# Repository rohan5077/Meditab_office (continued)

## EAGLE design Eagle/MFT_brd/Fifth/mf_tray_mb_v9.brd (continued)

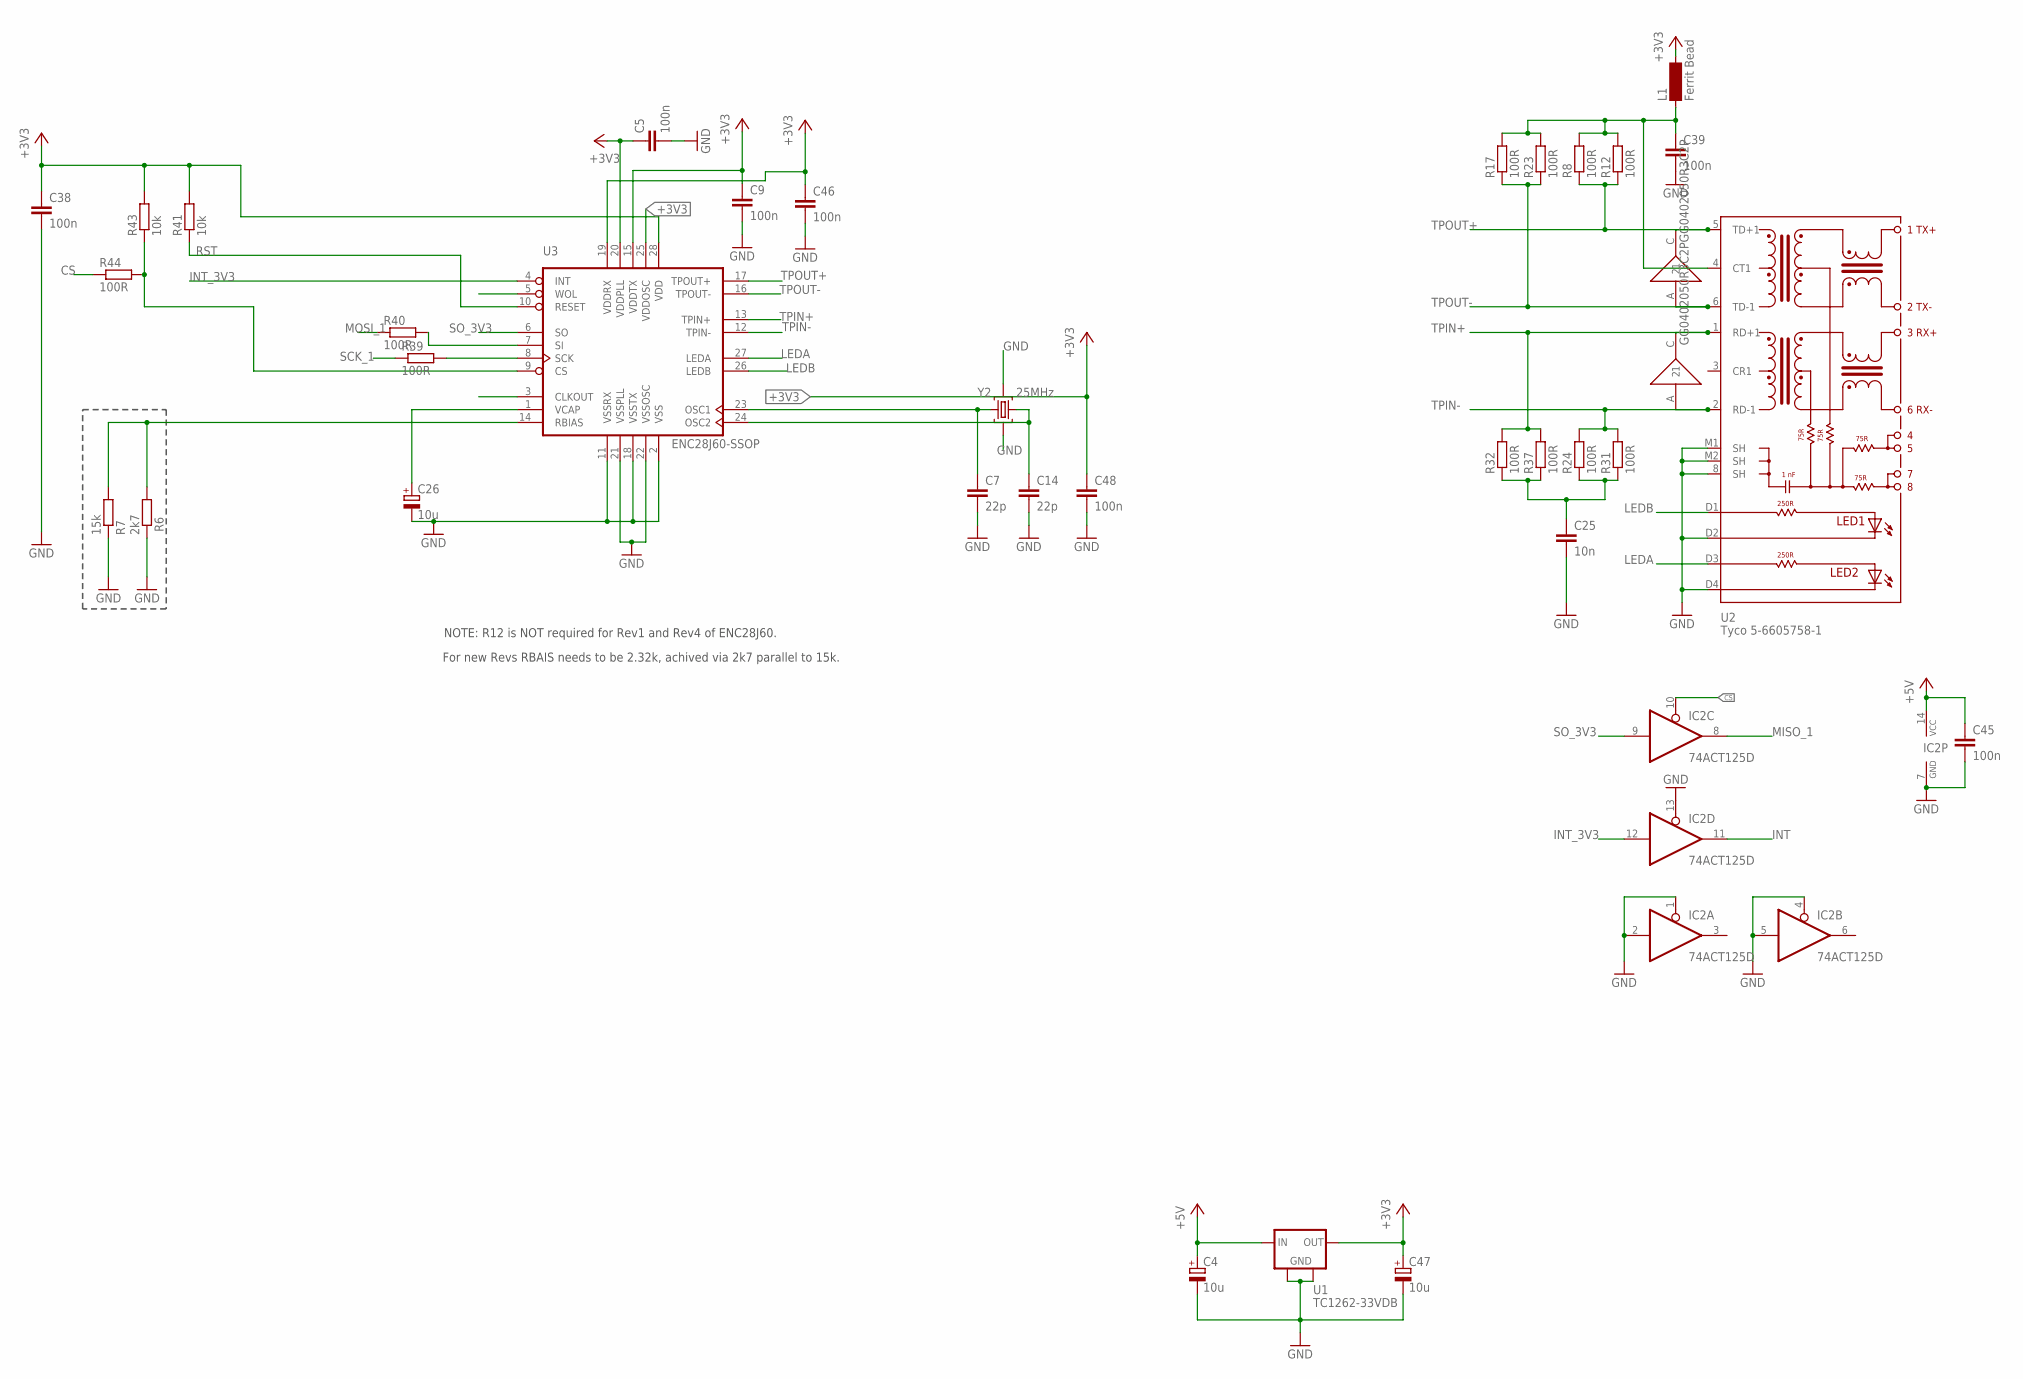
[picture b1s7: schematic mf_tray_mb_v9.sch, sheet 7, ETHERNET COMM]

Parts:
C4, C26, C47: 10u; 153CLV-0605
C5, C9, C38, C39, C45, C46, C48: 100n; C0603
C7, C14: 22p; C0603
C25: 10n; C0603
IC2: 74ACT125D; SO14
L1: Ferrit Bead; SM-1206
R6: 2k7; R0603
R7: 15k; R0603
R8, R12, R17, R23, R24, R31, R32, R37, R39, R40, R44: 100R; R0603
R41, R43: 10k; R0603
U1: TC1262-33VDB; SOT223
U2: Tyco 5-6605758-1; 5-6605758-1
U3: ENC28J60-SSOP; SSOP28
U$6, U$7: GG0402050R3C2P; 0402
Y2: 25MHz; CRYSTAL-3.2-2.5

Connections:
+3V3: C5.1, C9.1, C38.1, C46.1, C47.+, C48.1, L1.2, R41.2, R43.2, U1.3 (OUT), U3.15 (VDDTX), U3.19 (VDDRX), U3.20 (VDDPLL), U3.25 (VDDOSC), U3.28 (VDD); also elsewhere on the board
+5V: C4.+, C45.1, IC2.14 (VCC), U1.1 (IN); also elsewhere on the board
CS: IC2.10 (OE), R44.2; also elsewhere on the board
GND: C4.-, C5.2, C7.2, C9.2, C14.2, C25.2, C26.-, C38.2, C39.2, C45.2, C46.2, C47.-, C48.2, IC2.1 (OE), IC2.2 (I), IC2.4 (OE), IC2.5 (I), IC2.7 (GND), IC2.13 (OE), R6.2, R7.2, U1.2 (GND), U1.4 (GND), U2.8 (SH), U2.D2, U2.D4, U2.M1 (SH), U2.M2 (SH), U3.2 (VSS), U3.11 (VSSRX), U3.18 (VSSTX), U3.21 (VSSPLL), U3.22 (VSSOSC), Y2.2 (GND), Y2.4 (GND); also elsewhere on the board
INT: IC2.11 (O); also elsewhere on the board
INT_3V3: IC2.12 (I), U3.4 (INT)
LEDA: U2.D3, U3.27 (LEDA)
LEDB: U2.D1, U3.26 (LEDB)
MISO_1: IC2.8 (O); also elsewhere on the board
MOSI_1: R40.2; also elsewhere on the board
unnamed: R6.1, R7.1, U3.14 (RBIAS)
unnamed: C7.1, U3.23 (OSC1), Y2.3 (C2)
unnamed: C25.1, R24.1, R31.1, R32.1, R37.1
unnamed: C39.1, L1.1, R8.2, R12.2, R17.2, R23.2, U2.4 (CT1)
unnamed: C14.1, U3.24 (OSC2), Y2.1 (C1)
unnamed: R43.1, R44.1, U3.9 (CS)
unnamed: R40.1, U3.7 (SI)
unnamed: R39.1, U3.8 (SCK)
unnamed: C26.+, U3.1 (VCAP)
RST: R41.1, U3.10 (RESET)
SCK_1: R39.2; also elsewhere on the board
SO_3V3: IC2.9 (I), U3.6 (SO)
TPIN+: R32.2, R37.2, U2.1 (RD+1), U3.13 (TPIN+), U$7.C (2)
TPIN-: R24.2, R31.2, U2.2 (RD-1), U3.12 (TPIN-), U$7.A (1)
TPOUT+: R8.1, R12.1, U2.5 (TD+1), U3.17 (TPOUT+), U$6.C (2)
TPOUT-: R17.1, R23.1, U2.6 (TD-1), U3.16 (TPOUT-), U$6.A (1)

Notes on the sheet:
NOTE: R12 is NOT required for Rev1 and Rev4 of ENC28J60.
For new Revs RBAIS needs to be 2.32k, achived via 2k7 parallel to 15k.

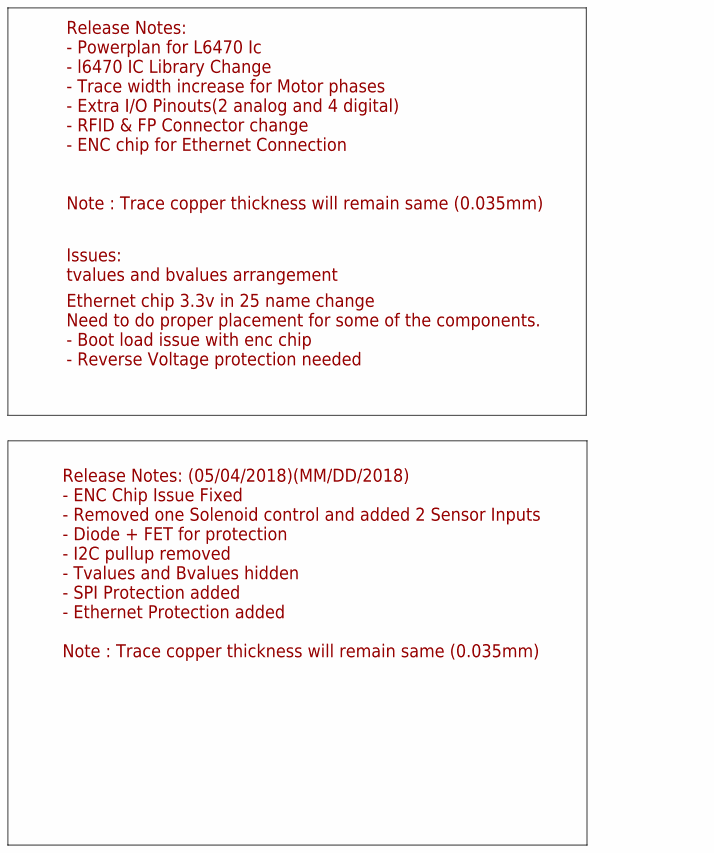
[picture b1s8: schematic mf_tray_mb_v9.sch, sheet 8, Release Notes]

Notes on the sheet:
Release Notes: - Powerplan for L6470 Ic - l6470 IC Library Change - Trace width increase for Motor phases - Extra I/O Pinouts(2 analog and 4 digital) - RFID & FP Connector change - ENC chip for Ethernet Connection Note : Trace copper thickness will remain same (0.035mm)
Issues:
tvalues and bvalues arrangement
Ethernet chip 3.3v in 25 name change
Need to do proper placement for some of the components.
- Boot load issue with enc chip
- Reverse Voltage protection needed
Release Notes: (05/04/2018)(MM/DD/2018) - ENC Chip Issue Fixed - Removed one Solenoid control and added 2 Sensor Inputs - Diode + FET for protection - I2C pullup removed - Tvalues and Bvalues hidden - SPI Protection added - Ethernet Protection added Note : Trace copper thickness will remain same (0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

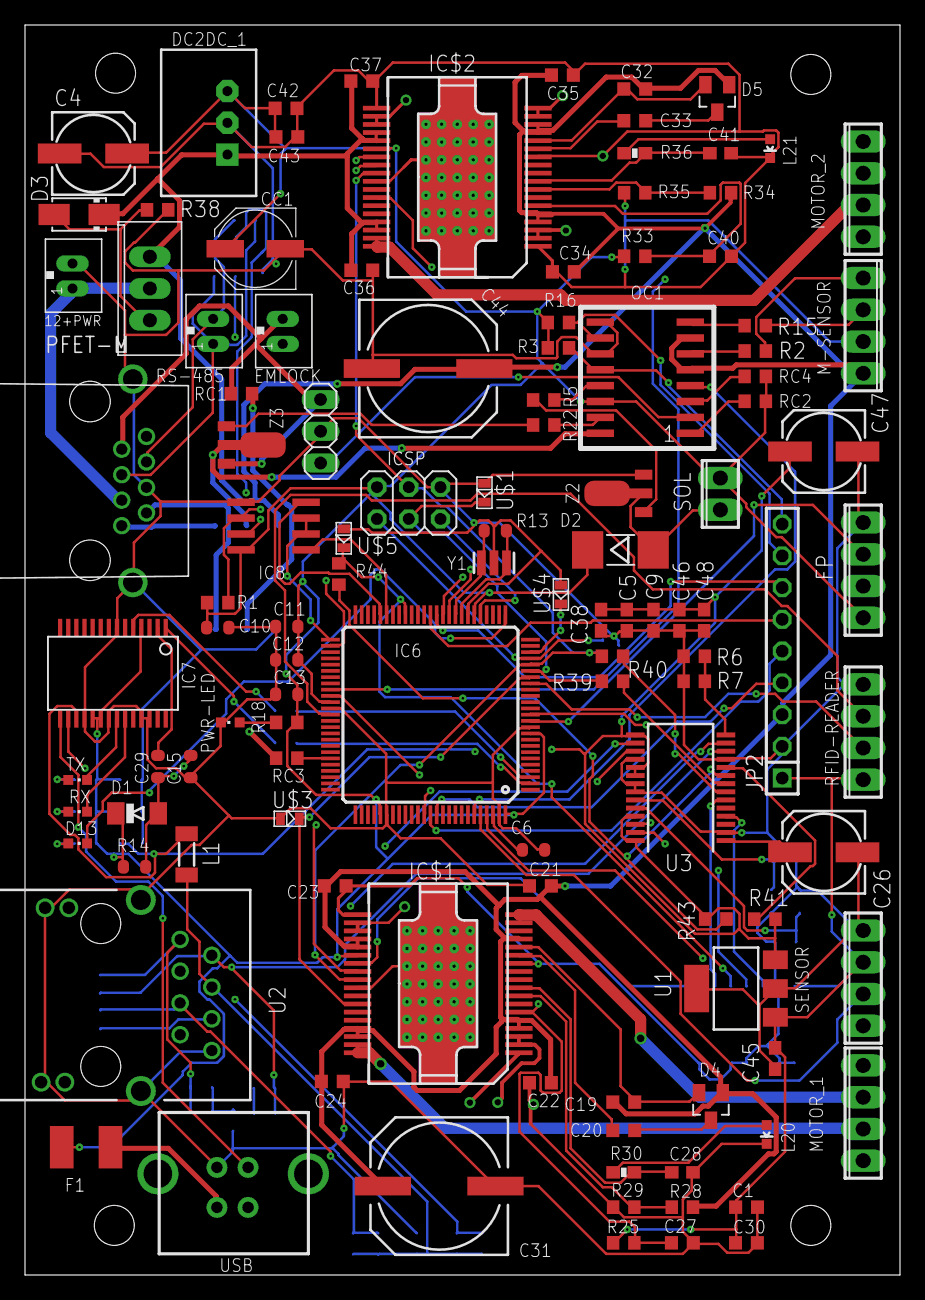
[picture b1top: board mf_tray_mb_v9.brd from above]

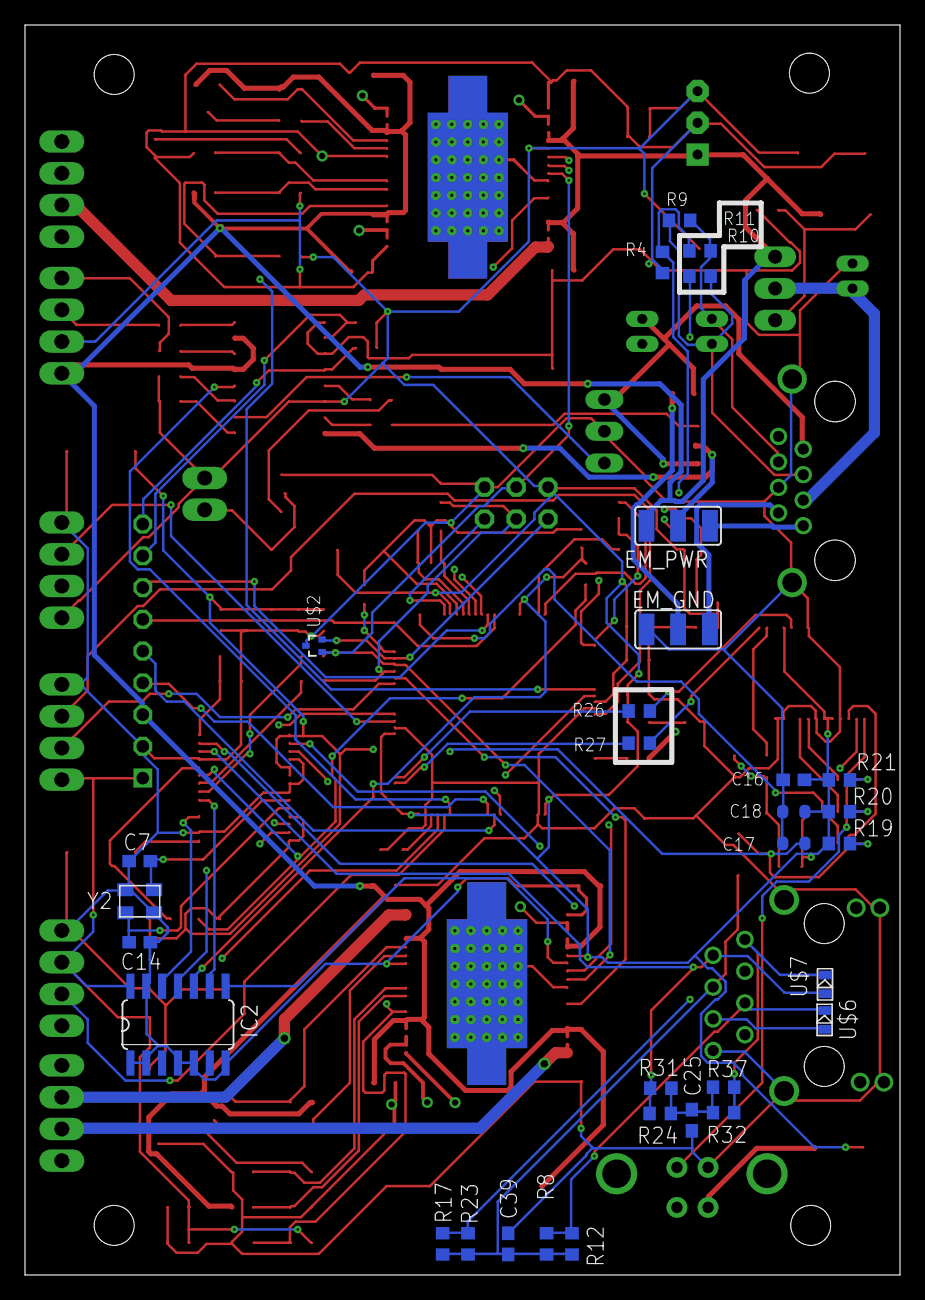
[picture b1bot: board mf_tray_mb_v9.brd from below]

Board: 4 copper layers, 70.0 x 100.0 mm, 146 parts (31 on the bottom side), 111 nets.

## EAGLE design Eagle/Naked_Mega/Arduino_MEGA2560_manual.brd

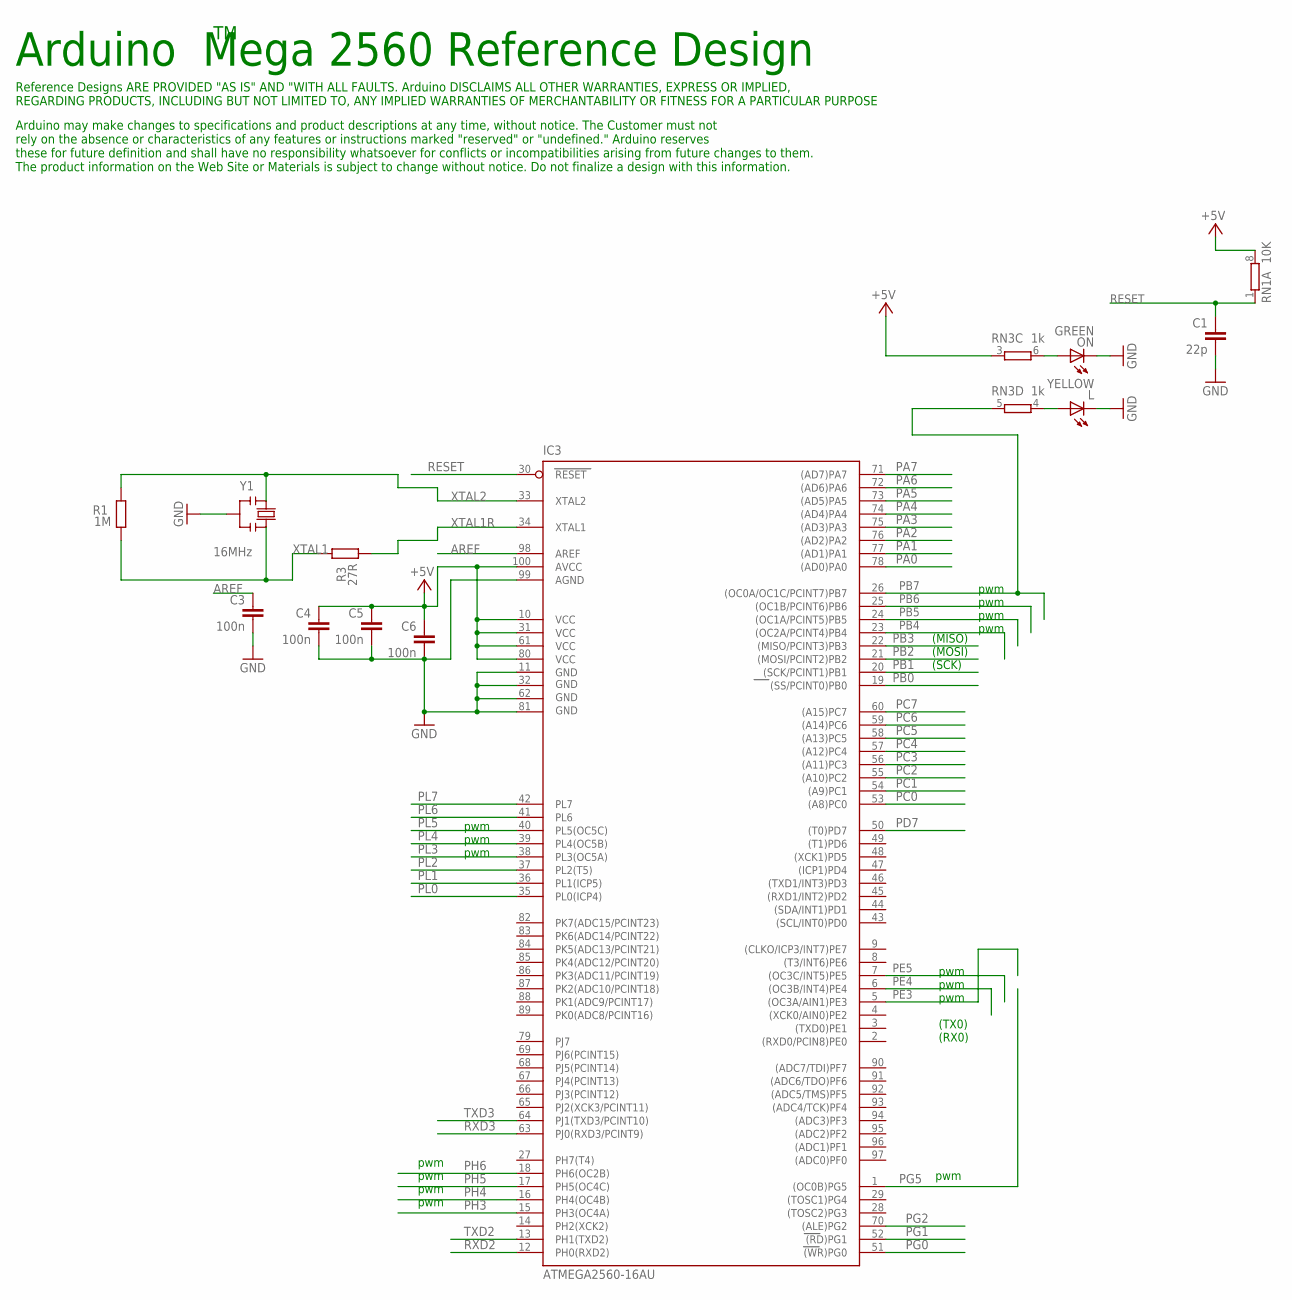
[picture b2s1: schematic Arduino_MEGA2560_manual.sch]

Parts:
C1: 22p; C0603-ROUND
C3, C4, C5, C6: 100n; C0603-ROUND
IC3: ATMEGA2560-16AU; TQFP100
L: YELLOW; CHIP-LED0805
ON: GREEN; CHIP-LED0805
R1: 1M; R0603-ROUND
R3: 27R; R0603-ROUND
RN1: 10K; CAT16
RN3: 1k; CAY16
Y1: 16MHz; RESONATOR

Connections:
+5V: C4.1, C5.1, C6.1, IC3.10 (VCC), IC3.31 (VCC1), IC3.61 (VCC2), IC3.80 (VCC3), IC3.100 (AVCC), RN1.8 (2), RN3.3 (1)
AREF: C3.1, IC3.98 (AREF)
GND: C1.2, C3.2, C4.2, C5.2, C6.2, IC3.11 (GND), IC3.32 (GND1), IC3.62 (GND2), IC3.81 (GND3), IC3.99 (AGND), L.C, ON.C, Y1.2
unnamed: L.A, RN3.4 (1)
unnamed: ON.A, RN3.6 (2)
PA0: IC3.78 ((AD0)PA0)
PA1: IC3.77 ((AD1)PA1)
PA2: IC3.76 ((AD2)PA2)
PA3: IC3.75 ((AD3)PA3)
PA4: IC3.74 ((AD4)PA4)
PA5: IC3.73 ((AD5)PA5)
PA6: IC3.72 ((AD6)PA6)
PA7: IC3.71 ((AD7)PA7)
PB0: IC3.19 ((SS/PCINT0)PB0)
PB1: IC3.20 ((SCK/PCINT1)PB1)
PB2: IC3.21 ((MOSI/PCINT2)PB2)
PB3: IC3.22 ((MISO/PCINT3)PB3)
PB4: IC3.23 ((OC2A/PCINT4)PB4)
PB5: IC3.24 ((OC1A/PCINT5)PB5)
PB6: IC3.25 ((OC1B/PCINT6)PB6)
PB7: IC3.26 ((OC0A/OC1C/PCINT7)PB7), RN3.5 (2)
PC0: IC3.53 ((A8)PC0)
PC1: IC3.54 ((A9)PC1)
PC2: IC3.55 ((A10)PC2)
PC3: IC3.56 ((A11)PC3)
PC4: IC3.57 ((A12)PC4)
PC5: IC3.58 ((A13)PC5)
PC6: IC3.59 ((A14)PC6)
PC7: IC3.60 ((A15)PC7)
PD7: IC3.50 ((T0)PD7)
PE3: IC3.5 ((OC3A/AIN1)PE3)
PE4: IC3.6 ((OC3B/INT4)PE4)
PE5: IC3.7 ((OC3C/INT5)PE5)
PG0: IC3.51 ((WR)PG0)
PG1: IC3.52 ((RD)PG1)
PG2: IC3.70 ((ALE)PG2)
PG5: IC3.1 ((OC0B)PG5)
PH3: IC3.15 (PH3(OC4A))
PH4: IC3.16 (PH4(OC4B))
PH5: IC3.17 (PH5(OC4C))
PH6: IC3.18 (PH6(OC2B))
PL0: IC3.35 (PL0(ICP4))
PL1: IC3.36 (PL1(ICP5))
PL2: IC3.37 (PL2(T5))
PL3: IC3.38 (PL3(OC5A))
PL4: IC3.39 (PL4(OC5B))
PL5: IC3.40 (PL5(OC5C))
PL6: IC3.41 (PL6)
PL7: IC3.42 (PL7)
RESET: C1.1, IC3.30 (RESET), RN1.1
RXD2: IC3.12 (PH0(RXD2))
RXD3: IC3.63 (PJ0(RXD3/PCINT9))
TXD2: IC3.13 (PH1(TXD2))
TXD3: IC3.64 (PJ1(TXD3/PCINT10))
XTAL1: R1.1, R3.2, Y1.3
XTAL1R: IC3.34 (XTAL1), R3.1
XTAL2: IC3.33 (XTAL2), R1.2, Y1.1

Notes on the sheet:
pwm
(TX0)
(RX0)
(MISO)
(SCK)
(MOSI)
Arduino Mega 2560 Reference Design
Arduino may make changes to specifications and product descriptions at any time, without notice. The Customer must not rely on the absence or characteristics of any features or instructions marked "reserved" or "undefined." Arduino reserves these for future definition and shall have no responsibili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
Reference Designs ARE PROVIDED "AS IS" AND "WITH ALL FAULTS. Arduino DISCLAIMS ALL OTHER WARRANTIES, EXPRESS OR IMPLIED, REGARDING PRODUCTS, INCLUDING BUT NOT LIMITED TO, ANY IMPLIED WARRANTIES OF MERCHANTABILITY OR FITNESS FOR A PARTICULAR PURPOSE

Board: 2 copper layers, 13 parts (0 on the bottom side), 10 nets, no tracks yet.

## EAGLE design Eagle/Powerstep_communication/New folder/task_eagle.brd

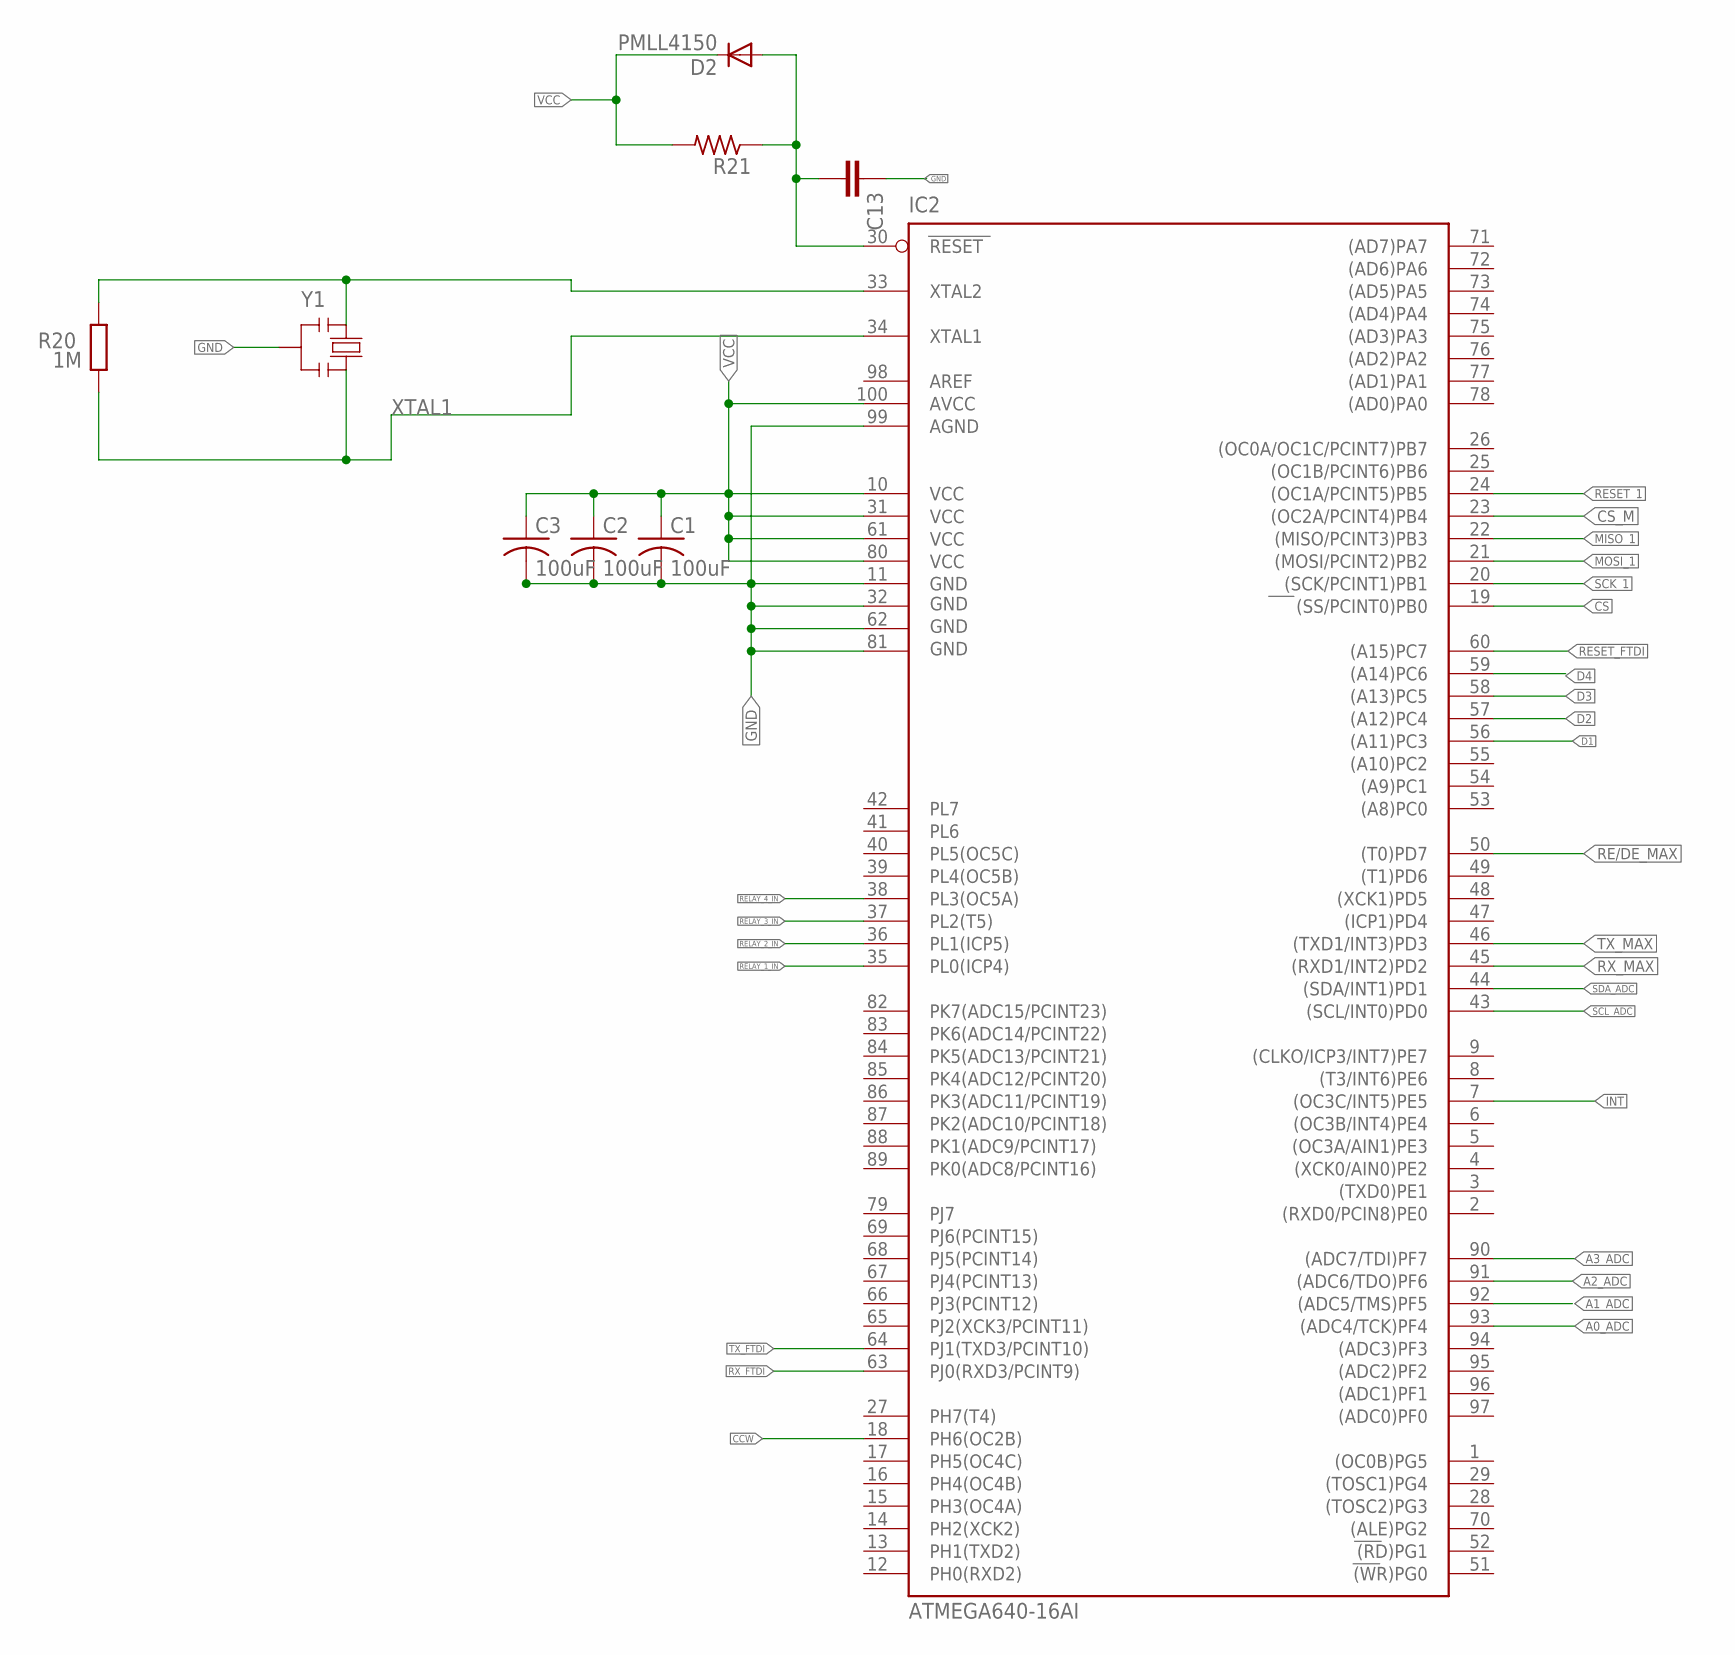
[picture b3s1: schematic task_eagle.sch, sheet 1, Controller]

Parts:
C1, C2, C3: 100uF; C0603
C13: CC0603; C0603
D2: PMLL4150; SOD80C
IC2: ATMEGA640-16AI; TQFP100
R20: 1M; R0603-ROUND
R21: R-US_R0603; R0603
Y1: RESONATORMU; RESONATOR

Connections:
CCW: IC2.18 (PH6(OC2B)); also elsewhere on the board
CS: IC2.19 ((SS/PCINT0)PB0); also elsewhere on the board
CS_M: IC2.23 ((OC2A/PCINT4)PB4); also elsewhere on the board
D1: IC2.56 ((A11)PC3); also elsewhere on the board
D2: IC2.57 ((A12)PC4); also elsewhere on the board
D3: IC2.58 ((A13)PC5); also elsewhere on the board
D4: IC2.59 ((A14)PC6); also elsewhere on the board
GND: C1.2, C2.2, C3.2, C13.1, IC2.11 (GND), IC2.32 (GND1), IC2.62 (GND2), IC2.81 (GND3), IC2.99 (AGND), Y1.2; also elsewhere on the board
INT: IC2.7 ((OC3C/INT5)PE5); also elsewhere on the board
MISO_1: IC2.22 ((MISO/PCINT3)PB3); also elsewhere on the board
MOSI_1: IC2.21 ((MOSI/PCINT2)PB2); also elsewhere on the board
unnamed: C13.2, D2.A, IC2.30 (RESET), R21.1
RE/DE_MAX: IC2.50 ((T0)PD7); also elsewhere on the board
RELAY_1_IN: IC2.35 (PL0(ICP4)); also elsewhere on the board
RELAY_2_IN: IC2.36 (PL1(ICP5)); also elsewhere on the board
RELAY_3_IN: IC2.37 (PL2(T5)); also elsewhere on the board
RELAY_4_IN: IC2.38 (PL3(OC5A)); also elsewhere on the board
RESET_1: IC2.24 ((OC1A/PCINT5)PB5); also elsewhere on the board
RESET_FTDI: IC2.60 ((A15)PC7); also elsewhere on the board
RX_FTDI: IC2.63 (PJ0(RXD3/PCINT9)); also elsewhere on the board
RX_MAX: IC2.45 ((RXD1/INT2)PD2); also elsewhere on the board
SCK_1: IC2.20 ((SCK/PCINT1)PB1); also elsewhere on the board
SCL_ADC: IC2.43 ((SCL/INT0)PD0); also elsewhere on the board
SDA_ADC: IC2.44 ((SDA/INT1)PD1); also elsewhere on the board
TX_FTDI: IC2.64 (PJ1(TXD3/PCINT10)); also elsewhere on the board
TX_MAX: IC2.46 ((TXD1/INT3)PD3); also elsewhere on the board
XTAL1: IC2.34 (XTAL1), R20.1, Y1.3
XTAL2: IC2.33 (XTAL2), R20.2, Y1.1

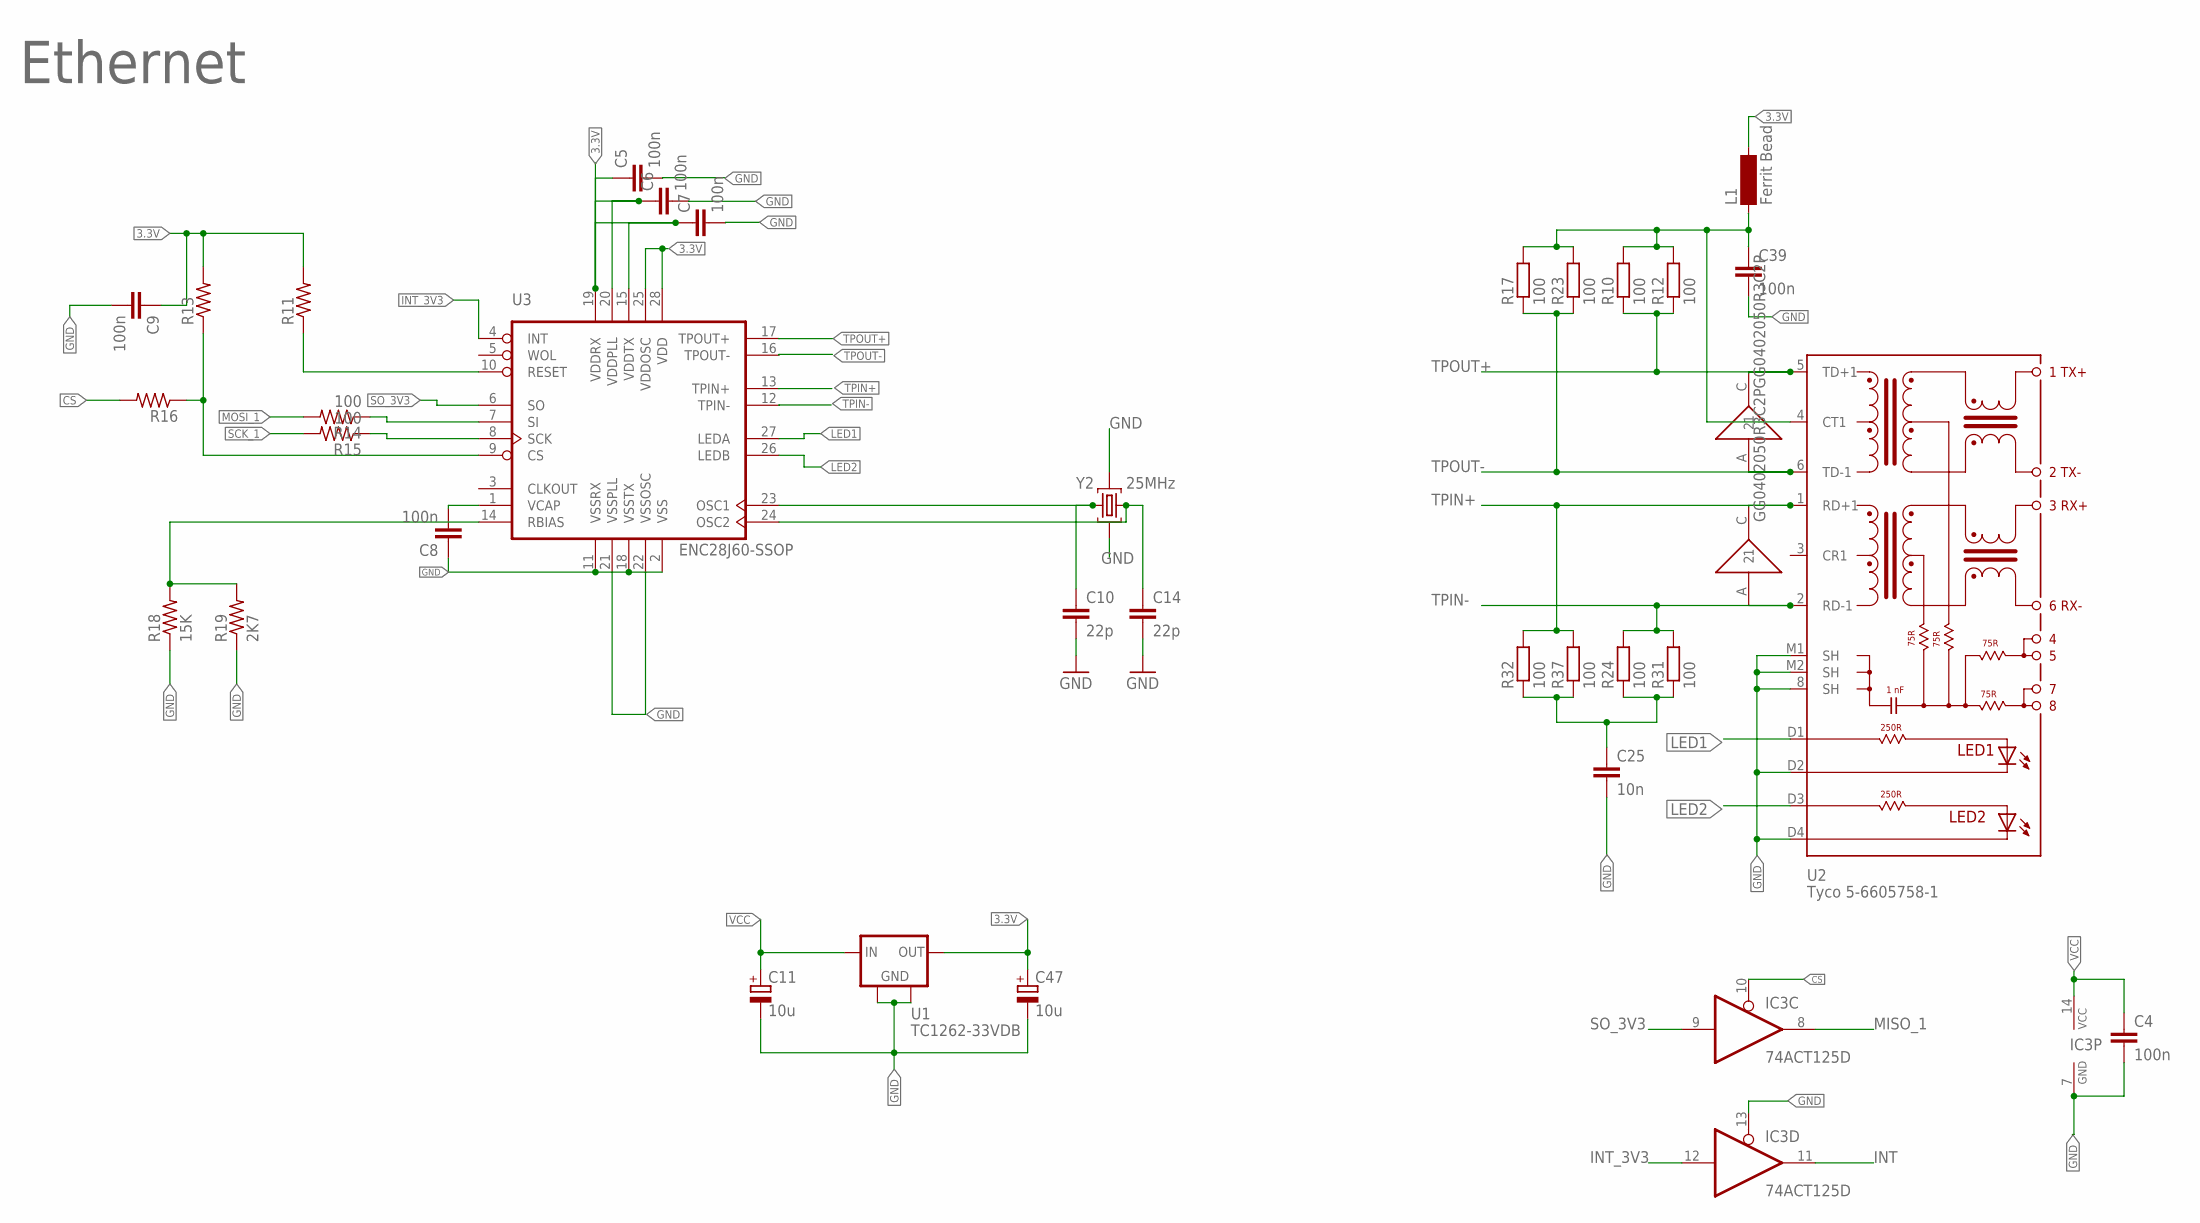
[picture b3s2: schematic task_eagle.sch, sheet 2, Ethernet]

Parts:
C4, C5, C6, C7, C8, C9, C39: 100n; C0603
C10, C14: 22p; C0603
C11, C47: 10u; 153CLV-0605
C25: 10n; C0603
IC3: 74ACT125D; SO14
L1: Ferrit Bead; SM-1206
R10, R12, R14, R15, R17, R23, R24, R31, R32, R37: 100; R0603
R11, R13, R16: R-US_R0603; R0603
R18: 15K; R0603
R19: 2K7; R0603
U1: TC1262-33VDB; SOT223
U2: Tyco 5-6605758-1; 5-6605758-1
U3: ENC28J60-SSOP; SSOP28
U$6, U$7: GG0402050R3C2P; 0402
Y2: 25MHz; CRYSTAL-3.2-2.5

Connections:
3.3V: C5.1, C6.1, C7.1, C9.1, C47.+, L1.2, R11.2, R13.2, U1.3 (OUT), U3.15 (VDDTX), U3.19 (VDDRX), U3.20 (VDDPLL), U3.25 (VDDOSC), U3.28 (VDD); also elsewhere on the board
CS: IC3.10 (OE), R16.2; also elsewhere on the board
GND: C4.2, C5.2, C6.2, C7.2, C8.1, C9.2, C10.2, C11.-, C14.2, C25.2, C39.2, C47.-, IC3.7 (GND), IC3.13 (OE), R18.1, R19.1, U1.2 (GND), U1.4 (GND), U2.8 (SH), U2.D2, U2.D4, U2.M1 (SH), U2.M2 (SH), U3.2 (VSS), U3.11 (VSSRX), U3.18 (VSSTX), U3.21 (VSSPLL), U3.22 (VSSOSC), Y2.2 (GND), Y2.4 (GND); also elsewhere on the board
INT: IC3.11 (O); also elsewhere on the board
INT_3V3: IC3.12 (I), U3.4 (INT)
LED1: U2.D1, U3.27 (LEDA)
LED2: U2.D3, U3.26 (LEDB)
MISO_1: IC3.8 (O); also elsewhere on the board
MOSI_1: R14.2; also elsewhere on the board
unnamed: R11.1, U3.10 (RESET)
unnamed: R13.1, R16.1, U3.9 (CS)
unnamed: R14.1, U3.7 (SI)
unnamed: R18.2, R19.2, U3.14 (RBIAS)
unnamed: R15.1, U3.8 (SCK)
unnamed: C8.2, U3.1 (VCAP)
unnamed: C10.1, U3.23 (OSC1), Y2.3 (C2)
unnamed: C25.1, R24.1, R31.1, R32.1, R37.1
unnamed: C39.1, L1.1, R10.2, R12.2, R17.2, R23.2, U2.4 (CT1)
unnamed: C14.1, U3.24 (OSC2), Y2.1 (C1)
SCK_1: R15.2; also elsewhere on the board
SO_3V3: IC3.9 (I), U3.6 (SO)
TPIN+: R32.2, R37.2, U2.1 (RD+1), U3.13 (TPIN+), U$7.C (2)
TPIN-: R24.2, R31.2, U2.2 (RD-1), U3.12 (TPIN-), U$7.A (1)
TPOUT+: R10.1, R12.1, U2.5 (TD+1), U3.17 (TPOUT+), U$6.C (2)
TPOUT-: R17.1, R23.1, U2.6 (TD-1), U3.16 (TPOUT-), U$6.A (1)

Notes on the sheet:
Ethernet

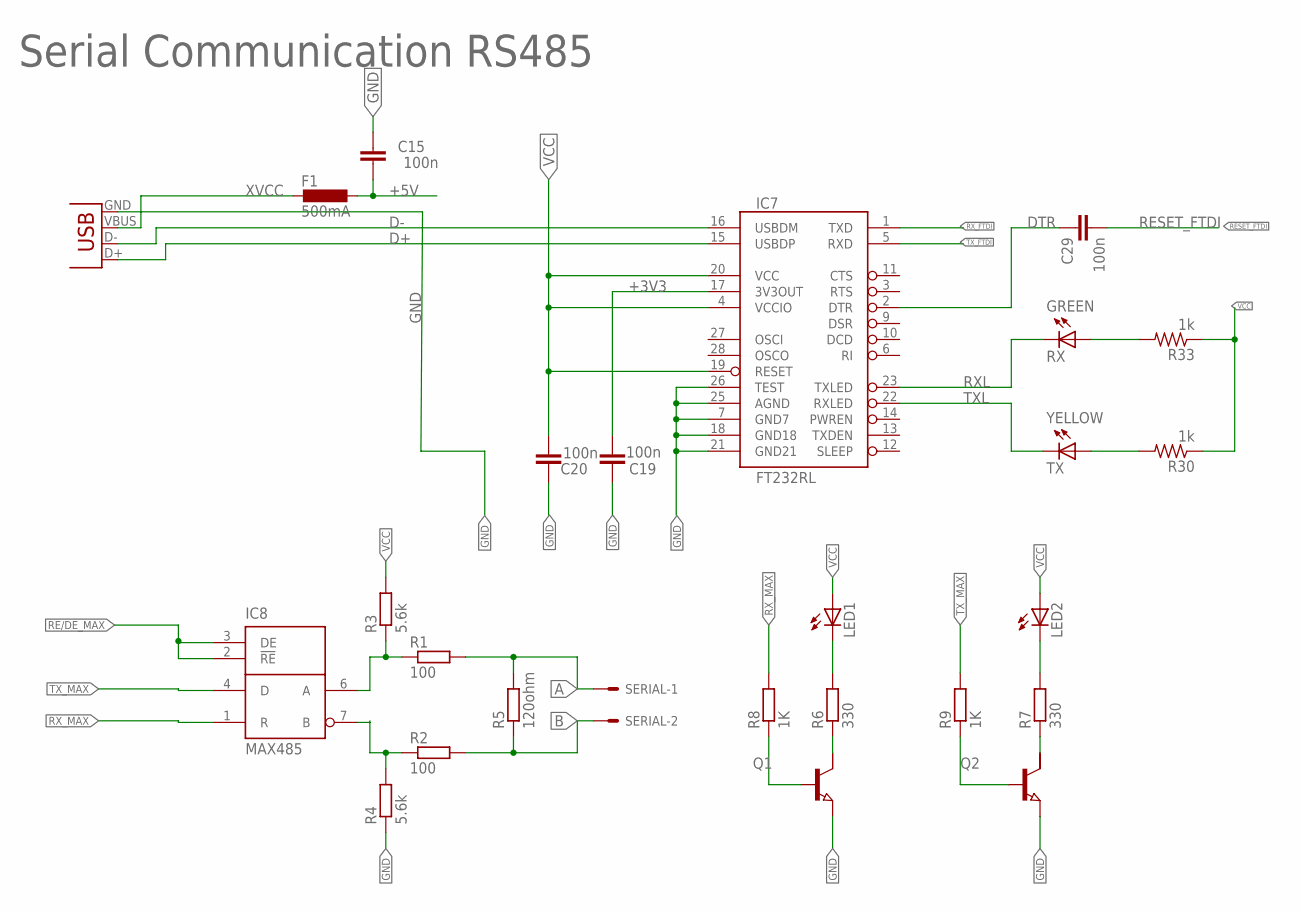
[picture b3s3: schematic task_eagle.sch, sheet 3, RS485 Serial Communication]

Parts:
C15: 100n; C0603
C19, C20, C29: 100n; C0603-ROUND
F1: 500mA; L1812
IC7: FT232RL; SSOP28DB
IC8: MAX485; SO-08
LED1, LED2: LED_ESML0603; LED_SML0603
Q1, Q2: NPN-TRANSISTIOR-2COLSOT89; SOT89
R1, R2: 100; R0603
R3, R4: 5.6k; R0603
R5: 120ohm; R0603
R6, R7: 330; R0603
R8, R9: 1K; R0603
R30, R33: 1k; R0603
RX: GREEN; CHIPLED_0603
SERIAL: KK-156-2
TX: YELLOW; CHIPLED_0603
USB: USB; USB-B-PTH-VERTICAL

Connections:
+3V3: C19.2, IC7.17 (3V3OUT)
A: R1.2, R5.2, SERIAL.1
B: R2.2, R5.1, SERIAL.2
D+: IC7.15 (USBDP), USB.D+
D-: IC7.16 (USBDM), USB.D-
DTR: C29.1, IC7.2 (DTR)
GND: C15.2, C19.1, C20.2, IC7.7 (GND7), IC7.18 (GND18), IC7.21 (GND21), IC7.25 (AGND), IC7.26 (TEST), IC8.5 (GND), Q1.3 (E), Q2.3 (E), R4.1, USB.GND; also elsewhere on the board
unnamed: IC8.6 (A), R1.1, R3.1
unnamed: IC8.7 (B), R2.1, R4.2
unnamed: R30.2, TX.A
unnamed: LED1.C, R6.2
unnamed: LED2.C, R7.2
unnamed: Q1.2 (C), R6.1
unnamed: Q2.2 (C), R7.1
unnamed: Q2.1 (B), R9.1
unnamed: Q1.1 (B), R8.1
unnamed: R33.2, RX.A
RE/DE_MAX: IC8.2 (!RE), IC8.3 (DE); also elsewhere on the board
RESET_FTDI: C29.2; also elsewhere on the board
RXL: IC7.23 (TXLED), RX.C
RX_FTDI: IC7.1 (TXD); also elsewhere on the board
RX_MAX: IC8.1 (R), R8.2; also elsewhere on the board
TXL: IC7.22 (RXLED), TX.C
TX_FTDI: IC7.5 (RXD); also elsewhere on the board
TX_MAX: IC8.4 (D), R9.2; also elsewhere on the board
XVCC: F1.2, USB.VBUS

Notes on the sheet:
Serial Communication RS485
